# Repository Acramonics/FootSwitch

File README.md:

FootSwitch
==========

This is a very small board to accommodate a standard 3PDT guitar pedal
footswitch and provide all wiring for true bypass:

- input (a stereo jack being used as a switch to short the ring to the
  sleeve when a mono plug is inserted)
- output (a mono jack)
- to/from the effects unit
- an (optional) LED
- power in
- power out
- an (optional) battery as an alternative power source.

It has been designed to have everything power-related on one side and
audio-related on the other.

The board has a solder jumper where the middle pad is shorted to `J`
(GND) or to `J/FS`. When shorted to `J`, only the jack switches the
power to the effects board on or off; when shorted to `J/FS`, both the
jack and the footswitch will switch off the power. (In other words,
the input jack plug must be inserted and the footswitch switched on in
order to power the effects.) If the effects take some time to become
active after powering on, then select `J`).

Molex KK254 style connectors are indicated, but not needed - you can
simpy solder wires to the holes in the board instead.

I prefer to mount the footswitch on the opposite side of the board
from the other components, but you can do whatever works for you!

KiCad
-----

To view/edit the KiCad files, you will need my ACRM symbol and
footprint libraries.

LED
---

If using the LED, you also need to add the `LED Res` resistor. The
value of this depends on the voltage drop of your LED (which will vary
with colour) and how bright you want it to be. 1K is a good starting
point for most LEDs.

Battery
-------

If you choose to use the optional battery power, then you need to add
`D2` - the anode location is indicated on the board rather than the
conventional indication of cathode although the `K` for the LED is
also the side where the `D2` cathode should be! This should be a
Schottky diode with at least a 9v rating and sufficient current to
power your effects board. Something like a 1N5819 or BAT86S will be
fine.

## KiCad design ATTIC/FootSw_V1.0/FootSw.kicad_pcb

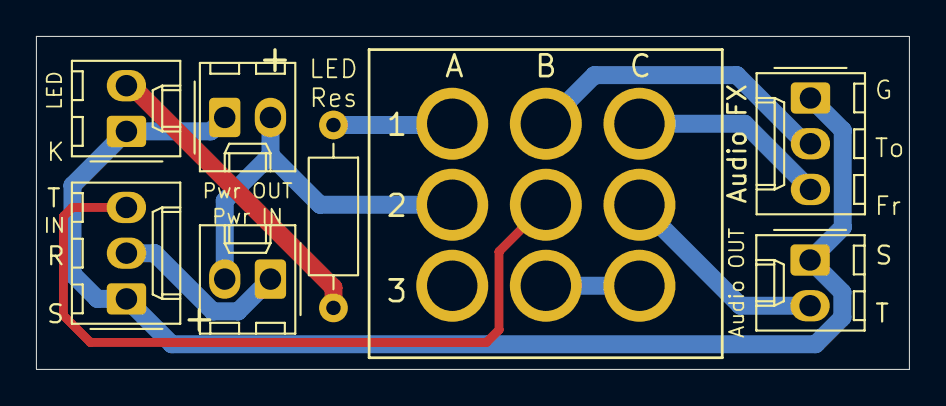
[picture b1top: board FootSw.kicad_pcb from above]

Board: 2 copper layers, 48.5 x 18.5 mm, 8 parts (0 on the bottom side), 10 nets.

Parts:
J1: IN; Molex_KK-254_AE-6410-03A_1x03_P2.54mm_Vertical
J2: Audio OUT; Molex_KK-254_AE-6410-02A_1x02_P2.54mm_Vertical
J4: Pwr IN; Molex_KK-254_AE-6410-02A_1x02_P2.54mm_Vertical
J5: LED; Molex_KK-254_AE-6410-02A_1x02_P2.54mm_Vertical
J7: Audio FX; Molex_KK-254_AE-6410-03A_1x03_P2.54mm_Vertical
J8: Pwr OUT; Molex_KK-254_AE-6410-02A_1x02_P2.54mm_Vertical
R1: 4K4; R_Axial_DIN0207_L6.3mm_D2.5mm_P10.16mm_Horizontal
SW1: SW_Foot_3PDT; 3PDT_FS

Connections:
GND: J1.1, J2.1, J5.1, J7.1, J8.1
unnamed: J1.2, J4.1
unnamed: J1.3, SW1.B2 (B)
unnamed: J2.2, SW1.C2 (B)
unnamed: J4.2, J8.2, SW1.A2 (B)
unnamed: J5.2, R1.2
unnamed: J7.2, SW1.B1 (A)
unnamed: J7.3, SW1.C1 (A)
unnamed: R1.1, SW1.A1 (A)
unnamed: SW1.B3 (C), SW1.C3 (C)

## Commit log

2025-09-02 Added images
2025-09-02 Updated README with images
2025-09-02 Corrected README image links
2025-09-02 Cropped 2d image
2025-09-02 Removed 2D image as the old version was cached in GitHub
2025-09-02 Added the 2D image back
